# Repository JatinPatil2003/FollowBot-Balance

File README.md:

# FollowBot-Balance
It is a Self balancing robot whhich has a feature of following human. It uses a control system to balance the bot and opencv and media pipe to detect human, it takes video stream from esp32cam and process that video and revert back coordinates of human to the server's ip address.

This Self balancing bot can balance at a point, can be contolled over remote and can hollow human

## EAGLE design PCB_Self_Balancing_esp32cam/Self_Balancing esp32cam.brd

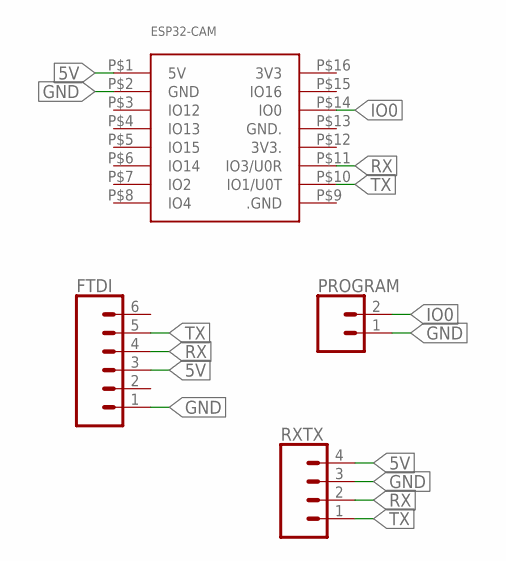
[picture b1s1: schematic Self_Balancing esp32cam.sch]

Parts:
ESP32-CAM: ESP32-CAM
FTDI: CONN_06SILK_FEMALE_PTH; 1X06
PROGRAM: CONN_02; 1X02
RXTX: CONN_04PTH; 1X04

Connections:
5V: ESP32-CAM.P$1 (5V), FTDI.3, RXTX.4
GND: ESP32-CAM.P$2 (GND), FTDI.1, PROGRAM.1, RXTX.3
IO0: ESP32-CAM.P$14 (IO0), PROGRAM.2
RX: ESP32-CAM.P$11 (IO3/U0R), FTDI.4, RXTX.2
TX: ESP32-CAM.P$10 (IO1/U0T), FTDI.5, RXTX.1

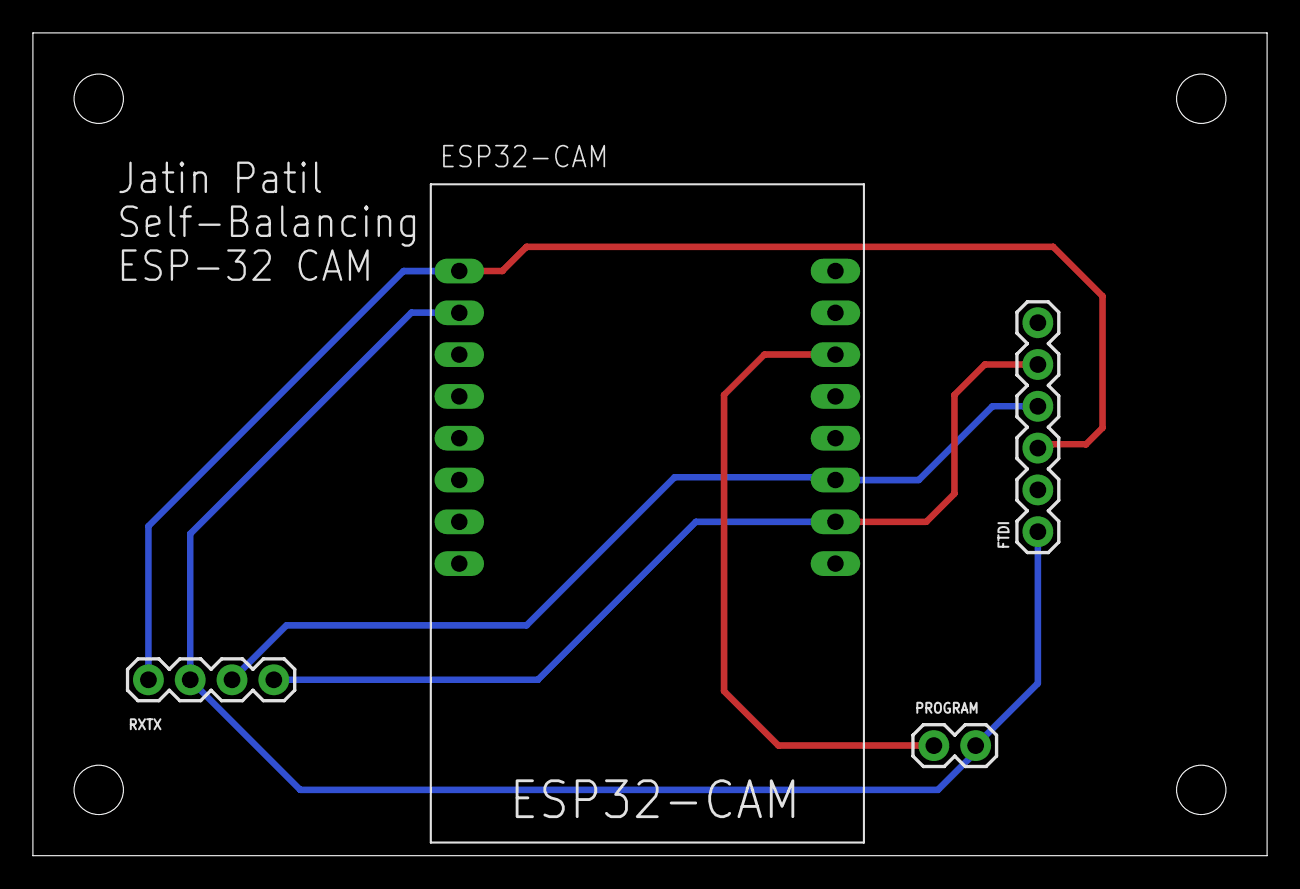
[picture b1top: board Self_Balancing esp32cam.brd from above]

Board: 2 copper layers, 75.0 x 50.0 mm, 4 parts (0 on the bottom side), 5 nets.

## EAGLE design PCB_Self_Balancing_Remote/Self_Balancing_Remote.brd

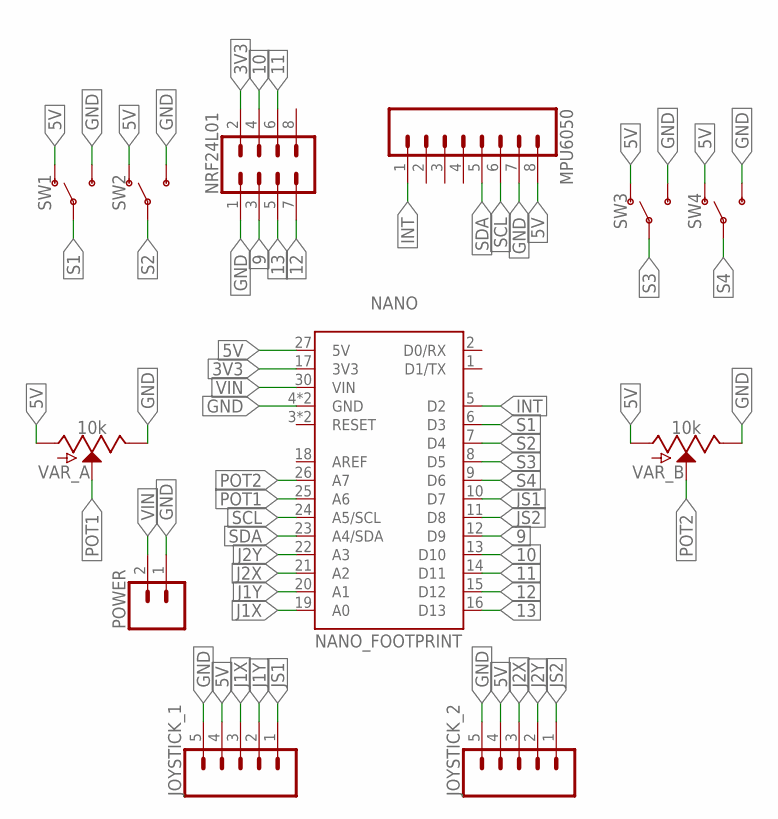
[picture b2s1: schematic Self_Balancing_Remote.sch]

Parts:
JOYSTICK_1, JOYSTICK_2: CONN_05; 1X05
MPU6050: CONN_08"; 1X08
NANO: NANO_FOOTPRINT; NANO
NRF24L01: CONN_04X2; 2X4
POWER: CONN_02; 1X02
SW1, SW2, SW3, SW4: SWITCH-SPDT-PTH-8.6X4.3MM; SWITCH_SPDT_8.6X4.3MM
VAR_A: 10k; POT-PTH-ALPS-KIT
VAR_B: 10k; POT-PTH-ALPS-KIT

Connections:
3V3: NANO.17 (3V3), NRF24L01.2
5V: JOYSTICK_1.4, JOYSTICK_2.4, MPU6050.8, NANO.27 (5V), SW1.1 (O), SW2.1 (O), SW3.1 (O), SW4.1 (O), VAR_A.P$3 (A), VAR_B.P$3 (A)
9: NANO.12 (D9), NRF24L01.3
10: NANO.13 (D10), NRF24L01.4
11: NANO.14 (D11), NRF24L01.6
12: NANO.15 (D12), NRF24L01.7
13: NANO.16 (D13), NRF24L01.5
GND: JOYSTICK_1.5, JOYSTICK_2.5, MPU6050.7, NANO.4 (GND), NANO.29 (GND), NRF24L01.1, POWER.1, SW1.3 (S), SW2.3 (S), SW3.3 (S), SW4.3 (S), VAR_A.P$1 (E), VAR_B.P$1 (E)
INT: MPU6050.1, NANO.5 (D2)
J1X: JOYSTICK_1.3, NANO.19 (A0)
J1Y: JOYSTICK_1.2, NANO.20 (A1)
J2X: JOYSTICK_2.3, NANO.21 (A2)
J2Y: JOYSTICK_2.2, NANO.22 (A3)
JS1: JOYSTICK_1.1, NANO.10 (D7)
JS2: JOYSTICK_2.1, NANO.11 (D8)
POT1: NANO.25 (A6), VAR_A.P$2 (S)
POT2: NANO.26 (A7), VAR_B.P$2 (S)
S1: NANO.6 (D3), SW1.2
S2: NANO.7 (D4), SW2.2
S3: NANO.8 (D5), SW3.2
S4: NANO.9 (D6), SW4.2
SCL: MPU6050.6, NANO.24 (A5/SCL)
SDA: MPU6050.5, NANO.23 (A4/SDA)
VIN: NANO.30 (VIN), POWER.2

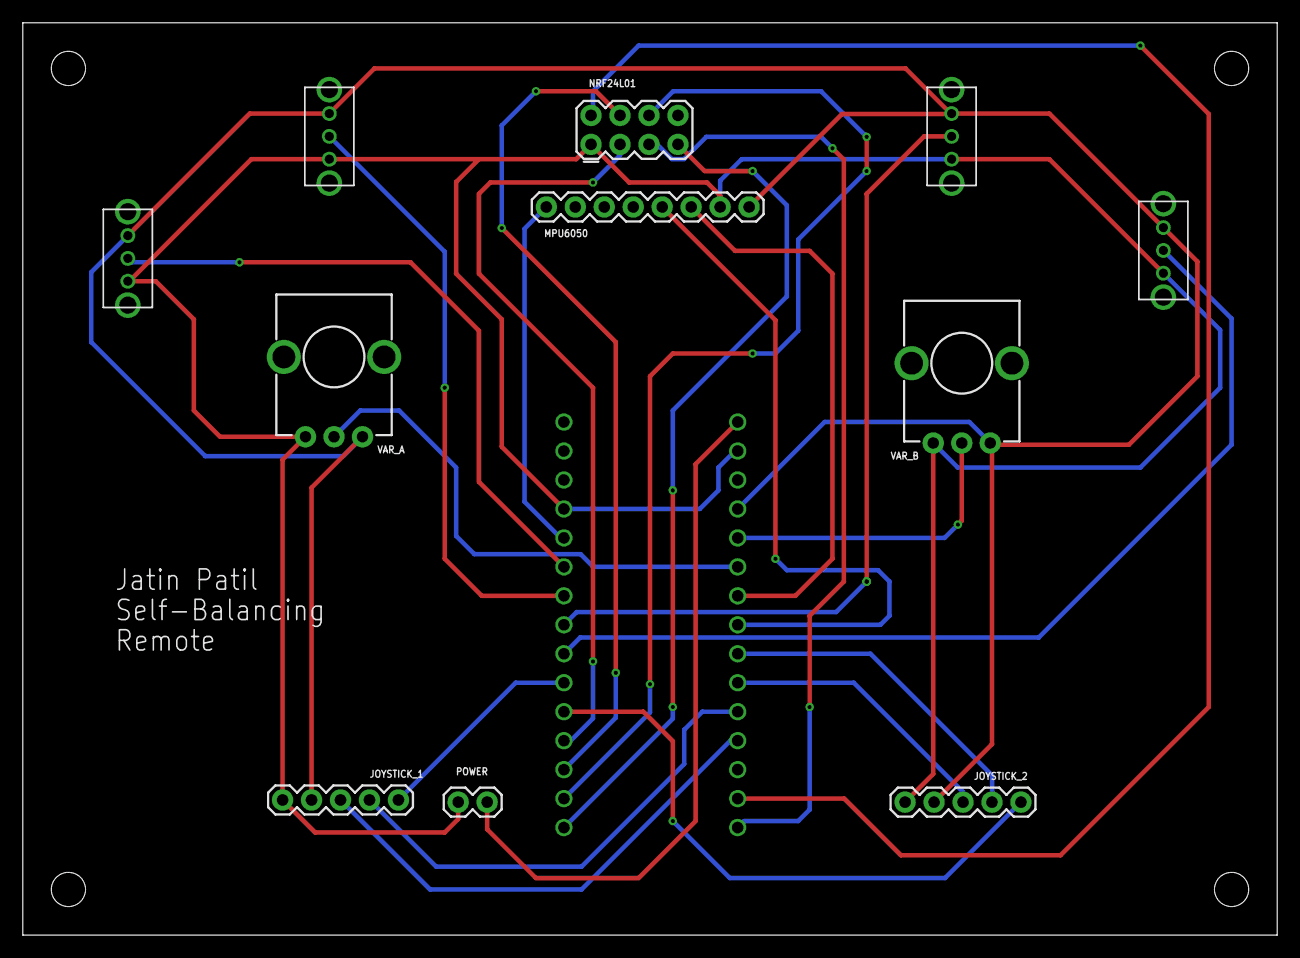
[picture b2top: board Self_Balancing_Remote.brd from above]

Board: 2 copper layers, 110.0 x 80.0 mm, 12 parts (0 on the bottom side), 24 nets.

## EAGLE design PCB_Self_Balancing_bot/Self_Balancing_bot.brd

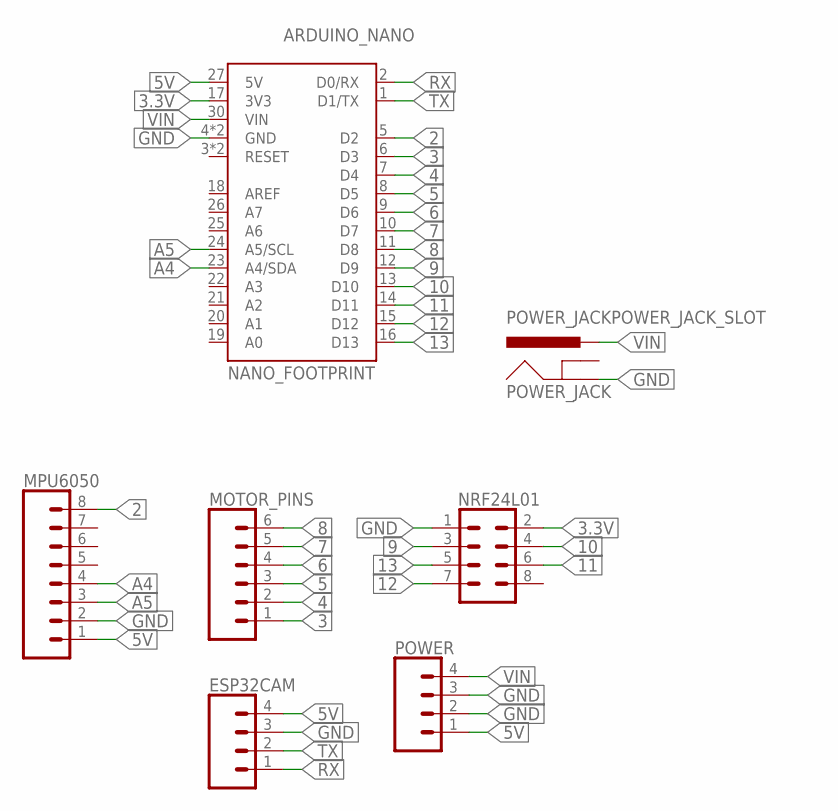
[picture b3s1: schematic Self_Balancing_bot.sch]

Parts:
ARDUINO_NANO: NANO_FOOTPRINT; NANO
ESP32CAM: CONN_04PTH; 1X04
MOTOR_PINS: CONN_06SILK_FEMALE_PTH; 1X06
MPU6050: CONN_08"; 1X08
NRF24L01: CONN_04X2; 2X4
POWER: CONN_04PTH; 1X04
POWER_JACK: POWER_JACKPOWER_JACK_SLOT; POWER_JACK_PTH_SLOT

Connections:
2: ARDUINO_NANO.5 (D2), MPU6050.8
3: ARDUINO_NANO.6 (D3), MOTOR_PINS.1
3.3V: ARDUINO_NANO.17 (3V3), NRF24L01.2
4: ARDUINO_NANO.7 (D4), MOTOR_PINS.2
5: ARDUINO_NANO.8 (D5), MOTOR_PINS.3
5V: ARDUINO_NANO.27 (5V), ESP32CAM.4, MPU6050.1, POWER.1
6: ARDUINO_NANO.9 (D6), MOTOR_PINS.4
7: ARDUINO_NANO.10 (D7), MOTOR_PINS.5
8: ARDUINO_NANO.11 (D8), MOTOR_PINS.6
9: ARDUINO_NANO.12 (D9), NRF24L01.3
10: ARDUINO_NANO.13 (D10), NRF24L01.4
11: ARDUINO_NANO.14 (D11), NRF24L01.6
12: ARDUINO_NANO.15 (D12), NRF24L01.7
13: ARDUINO_NANO.16 (D13), NRF24L01.5
A4: ARDUINO_NANO.23 (A4/SDA), MPU6050.4
A5: ARDUINO_NANO.24 (A5/SCL), MPU6050.3
GND: ARDUINO_NANO.4 (GND), ARDUINO_NANO.29 (GND), ESP32CAM.3, MPU6050.2, NRF24L01.1, POWER.2, POWER.3, POWER_JACK.GND
RX: ARDUINO_NANO.2 (D0/RX), ESP32CAM.1
TX: ARDUINO_NANO.1 (D1/TX), ESP32CAM.2
VIN: ARDUINO_NANO.30 (VIN), POWER.4, POWER_JACK.PWR

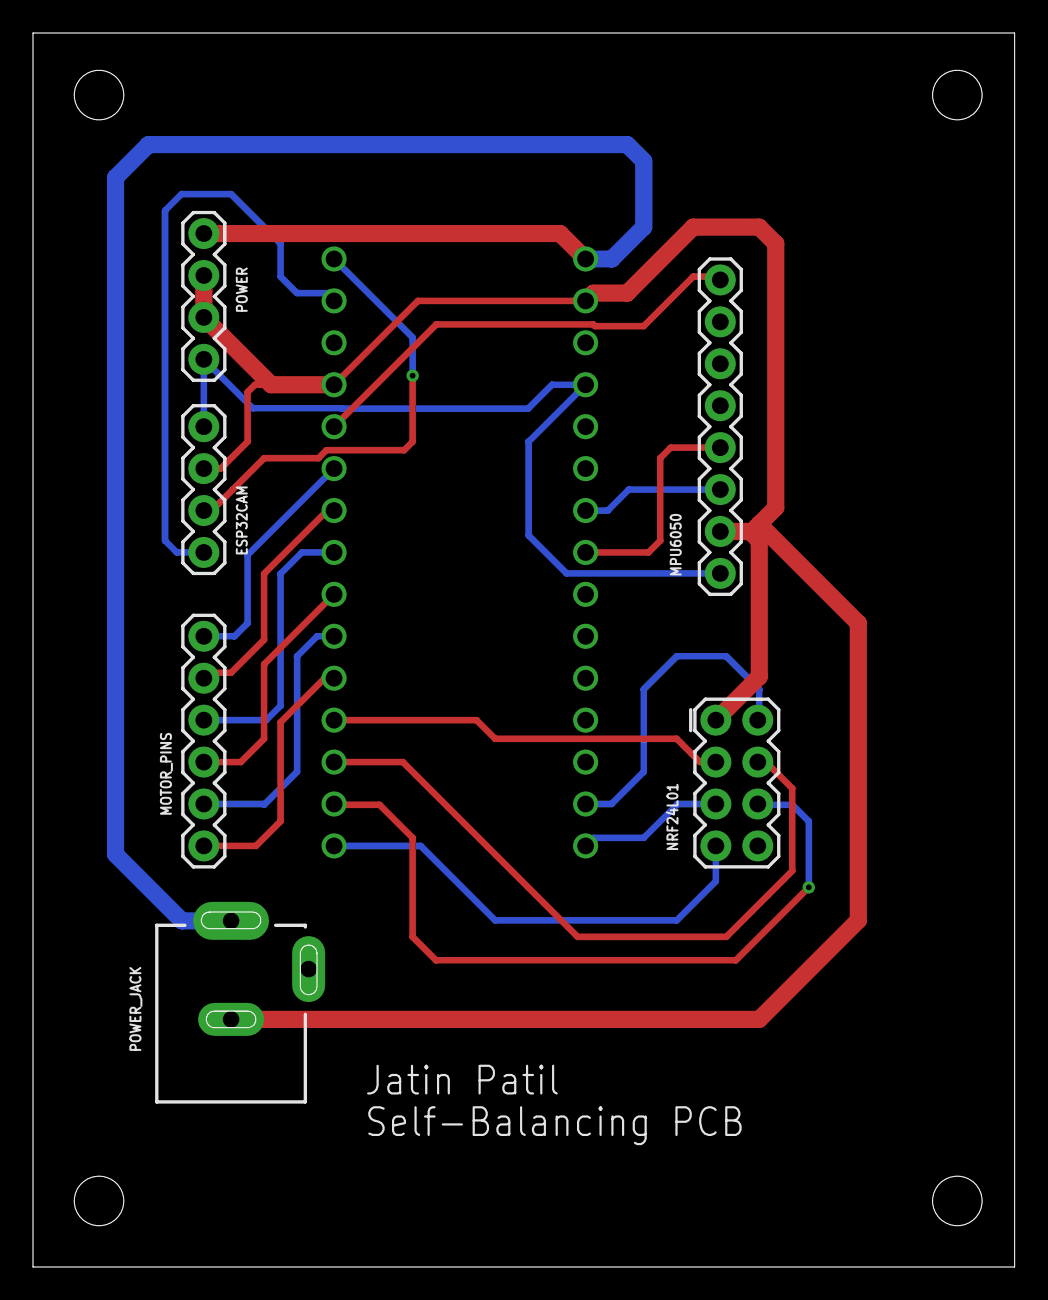
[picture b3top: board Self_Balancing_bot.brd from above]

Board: 2 copper layers, 59.5 x 74.8 mm, 7 parts (0 on the bottom side), 20 nets.

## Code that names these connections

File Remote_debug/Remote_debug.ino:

#define switchPin1 3
#define switchPin2 4
#define switchPin3 5
#define switchPin4 6
#define potPin1 A7
#define potPin2 A6
#define joyPin1_1 A2
#define joyPin1_2 A3
#define joyPin2_1 A0
#define joyPin2_2 A1
struct nrfdata{
  int S1,S2,S3,S4;
  int Pot1,Pot2;
  int J1X,J1Y,J2X,J2Y;
}data;


void setup() {
  // put your setup code here, to run once:
  pinMode(switchPin1,INPUT);
  pinMode(switchPin2,INPUT);
  pinMode(switchPin3,INPUT);
  pinMode(switchPin4,INPUT);
  Serial.begin(9600);
}

void loop() {
  // put your main code here, to run repeatedly:
  data.S1 = digitalRead(switchPin1);
  data.S2 = digitalRead(switchPin2);
  data.S3 = digitalRead(switchPin3);
  data.S4 = digitalRead(switchPin4);
  data.Pot1 = analogRead(potPin1);
  data.Pot2 = analogRead(potPin2);
  data.J1X = analogRead(joyPin1_1);
  data.J1Y = analogRead(joyPin1_2);
  data.J2X = analogRead(joyPin2_1);
  data.J2Y = analogRead(joyPin2_2);
  delay(100);
  Serial.print("----------------------------------------\n");
  Serial.print(" | ");
  Serial.print(data.J1X);
  Serial.print(" | ");
  Serial.print(data.J1Y);
  Serial.print(" | ");
  Serial.print(data.J2X);
  Serial.print(" | ");
  Serial.print(data.J2Y);
  Serial.print(" | ");
  Serial.print(data.Pot1);
  Serial.print(" | ");
  Serial.print(data.Pot2);
  Serial.print(" | ");
  Serial.print(data.S1);
  Serial.print(" | ");
  Serial.print(data.S2);
  Serial.print(" | ");
  Serial.print(data.S3);
  Serial.print(" | ");
  Serial.print(data.S4);
  Serial.print("\n");
}

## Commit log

2023-03-21 uploaded all files
    sharing of human coordinates between Arduino nano and esp32cam is remaining

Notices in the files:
parts and their libraries:
SparkFun-Connectors: Licensing: Creative Commons ShareAlike 4.0 International - https://creativecommons.org/licenses/by-sa/4.0
